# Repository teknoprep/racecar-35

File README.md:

# racecar-35

Two-MCU dash for a track car.

**Latest Rev C target:** add a third MCU—an on-board ESP32-S3 WiFi coprocessor—to
upload directly from Teensy SD over local SPI, while the screen keeps WiFi for
unchanged OTA and optional upload fallback. Add a replaceable CR2032 on Teensy VBAT
for RTC retention. This is an architecture update, **not an implemented new uplink**;
see [WiFi/RTC requirements](hardware/teensy-integrated-revc/WIFI_RTC_ARCHITECTURE.md).
Rev C has an **internal WiFi PCB antenna** and **all screw terminals on the LEFT
edge**, labelled by function/pin. **Actual 130 × 140 mm routed electrical CAD,
Gerber/drill ZIP, BOM, assembly documents and an assembled view now exist:**
[Rev C engineering prototype](hardware/teensy-integrated-revc/README.md).
It passes ERC/DRC/netlist checks but is unbuilt and not independently approved;
new WiFi firmware, oil/coolant conversions and bench validation remain.
A/B are retired under `hardware/_archive/`, not alternative orderable designs.

**WiFi-only on the CrowPanel since v0.1.148.** Ethernet/W5500 support
and the Internet-route setting have been removed. WiFi credentials/status are
always visible; old saved Ethernet selections are ignored. NTP/OTA/uploads run
through the screen. See [CLAUDE.md](CLAUDE.md) and [BUILD.md](BUILD.md) for current
architecture/toolchains; much of the original overview below is historical.
The integrated Rev C board is an unbuilt electrical prototype. **v0.1.149 source adds
opt-in AFR/lambda logging from the external AEM 30-0300 gauge output** (WHITE signal
and BROWN reference), not a direct oxygen sensor. A protected/scaled ADC input
is implemented in Rev C with clamps and powered-off isolation, but requires
independent review and physical validation. See
[AFR_INTERFACE.md](hardware/teensy-integrated-revc/AFR_INTERFACE.md).

```
+--------------+   Serial2 (UART)   +--------------+   Serial3 (UART)   +--------------+
|              |  pin 7 RX2 / 8 TX2 |              | pin 14 TX3 / 15 RX |              |
|  u-blox GNSS | <----------------> | Teensy 4.1   | -----------------> | CrowPanel S3 |
|              |   38400/9600 baud  |              |    115200 baud     |  7" 800x480  |
+--------------+                    +--------------+                    +--------------+
                                                                         (LovyanGFX UI)
```

The Teensy reads GNSS PVT data from a SparkFun u-blox module and publishes
ASCII CSV lines on Serial3. The CrowPanel ESP32-S3 listens on UART0 and
renders the dash with LovyanGFX. UART is one-way, Teensy → CrowPanel.

## Repository layout

| Path | Project | Target |
| --- | --- | --- |
| `platformio.ini`, `src/main.cpp` | Teensy firmware | Teensy 4.1 |
| `crowpanel-ui/platformio.ini`, `crowpanel-ui/src/main.cpp` | Dash UI | CrowPanel ESP32-S3 7" v3.0 |

Each subproject is its own PlatformIO env. Build them from their own
directory.

## Wire protocol

ASCII CSV lines, `\n`-terminated, 115200 8N1, ~5 Hz:

```
GPS,<fix>,<sats>,<lat_deg>,<lon_deg>,<speed_mph>,<heading_deg>
```

| Field | Meaning |
| --- | --- |
| `fix` | 0=None 1=DR 2=2D 3=3D 4=3D+DR 5=Time-only |
| `sats` | satellites in view |
| `lat_deg`, `lon_deg` | decimal degrees, 6 decimals |
| `speed_mph` | mph, 1 decimal |
| `heading_deg` | course over ground in degrees, 1 decimal |

Example: `GPS,3,12,40.123456,-74.123456,67.5,123.4`

## Wiring

| Link | From | To |
| --- | --- | --- |
| GPS → Teensy | u-blox TX | Teensy pin 7 (Serial2 RX) |
| Teensy → GPS | Teensy pin 8 (Serial2 TX) | u-blox RX |
| Teensy → Dash | Teensy pin 14 (Serial3 TX) | CrowPanel UART0 RX (GPIO 44) |
| Dash → Teensy | Teensy pin 15 (Serial3 RX) | CrowPanel UART0 TX (GPIO 43) |
| Common ground | Teensy GND | CrowPanel GND |
| Power | USB-C to CrowPanel | (Teensy powered separately by its own USB) |

Teensy ↔ CrowPanel is two devices both on 3.3 V logic — no level shifter.
A common ground is required.

## Flashing

### Teensy firmware

```powershell
pio run -t upload
```

The first time, you may need to physically tap the program button on the
Teensy. After that, `teensy_reboot` resets the board over USB.

### CrowPanel firmware

> [!IMPORTANT]
> **Disconnect the two UART jumpers between the Teensy and the CrowPanel
> before flashing the CrowPanel.** UART0 (GPIO 43/44) is shared with the
> CH340 USB-serial chip used to upload firmware. If the Teensy is
> connected, both devices will drive the same wire and the upload will
> fail or corrupt.

```powershell
cd crowpanel-ui
pio run -t upload
```

After the upload finishes ("Hash of data verified"), unplug USB-C, wire
the Teensy back in, then power the CrowPanel via USB-C again.

## End-to-end smoke test

1. Flash both firmwares (Teensy first or CrowPanel first, doesn't matter).
2. Wire everything per the table above. Double-check common GND.
3. Power the CrowPanel via USB-C. The dash should boot and show 0.0 mph
   with `LINK STALE` in red — that's correct: nothing on the wire yet.
4. Plug in the Teensy. Within a second, `LINK` should turn green and you
   should see the speed/heading/lat/lon updating at ~5 Hz, even with no
   GPS fix yet (those fields will read 0 until `FIX` shows `2D`/`3D`).
5. Take it outside or near a window. `FIX` will go yellow → green and
   `SATS` will climb as the module gets a fix.

## Debugging

- Open `pio device monitor` on the Teensy to see the same CSV stream the
  Teensy is sending — useful for confirming the GPS half is working
  before chasing UART issues on the dash side.
- Open `pio device monitor` on the CrowPanel (with the Teensy
  disconnected, and a `Serial.print` of incoming bytes added if you want
  to see what's hitting UART0). Note that with `ARDUINO_USB_CDC_ON_BOOT=0`
  the CrowPanel's `Serial` object IS UART0 — the same wire the Teensy
  uses — so you can't tap it from USB and the Teensy at the same time.
- If the panel boots black, retry the power-only test (USB-C only, no
  Teensy wires) to confirm the panel itself is alive before suspecting
  firmware.

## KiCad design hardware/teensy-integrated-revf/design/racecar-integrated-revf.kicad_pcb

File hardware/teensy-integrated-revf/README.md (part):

# Rev F — four-layer integrated trunk logger

**UNBUILT ENGINEERING PROTOTYPE. NOT INDEPENDENTLY REVIEWED OR PHYSICALLY
VALIDATED.** A clean CAD report is not electrical approval, a thermal test, an
RF measurement, or evidence that the board works.

Produced to close three gaps in Rev C: the missing Raspberry Pi video UART and the
missing throttle-position and brake-pressure analog inputs.

**Rev E closed two more:** the 5 V rail is **our own TPS54560B converter** instead of a
Pololu module that could not be sourced, and the **car's own input voltage is measured on
the board** instead of being inferred from the ECU or a Bluetooth dongle.

**Rev F closes the CAN gap.** The external SN65HVD230 plug-in module and its `J7` header
are **deleted**; a **TCAN1042HGV-Q1** is soldered on with its **STB pin hard-tied to GND**,
and `J14` presents `CANH` / `CANL` / `GND` with switchable split termination. See
[Onboard CAN (Rev F)](#onboard-can-rev-f--no-plug-in-module).

## Deliverable

- **`Racecar-RevF-GERBERS-ENGINEERING-PROTOTYPE.zip`** — 11 Gerber layers
  (4 copper + both masks/silkscreens/pastes + Edge.Cuts), separate metric
  **PTH and NPTH** Excellon drills with maps, schematic PDF, BOM, assembly
  positions CSV, fabrication/assembly/bring-up notes, editable CAD, validation
  reports and a SHA-256 manifest. Verified CRC and per-file hashes.
- **`Racecar-RevF-3D.html`** — the whole board in 3D as **one self-contained file**
  (1.5 MB): orbit/zoom, a clickable list of what is fitted, and labels on the parts.
  No server, no CDN, no network — open it from anywhere, or send it to someone.
- **`Racecar-RevF-3D.glb`** — the same board as a standard glTF model (5.4 MB),
  for Blender, Windows 3D Viewer, any online glTF viewer, a fab/shop or a case
  designer. Plain glTF 2.0, no extensions to install.
- **`Racecar-RevF-3D-preview.png`** — still image of the viewer, for documents.

### Rebuilding the 3D outputs

```bash
cd hardware/teensy-integrated-revf
python3 electrical/export3d.py      # presentation copy + Racecar-RevF-3D.glb (+ raw copper)
python3 electrical/make_3d_share.py # the single-file viewer (needs node + a local three)
cp render/Racecar-RevF-3D.glb render/Racecar-RevF-3D.html .
/home/chris/racecar-tools/servervenv/bin/python3 electrical/render_stills.py
                                    # render/check/{top,angle}.png + Racecar-RevF-3D-preview.png
```

The 3D outputs carry whatever silkscreen `design/` holds, so re-run all four steps after a
silk change (the stills used to lag the board: they still showed the 2026-10-11 silk).

Both scripts work on a **copy**; the routed CAD in `design/` is hashed before and
after and is never modified by them. Every model substitution, the generated bodies and
the caveats are recorded in `render/3D-EXPORT-REPORT.json` for audit.

**How the bodies were obtained (and what is not real):**

* KiCad's official 3D library supplies the STEP bodies (`sudo apt-get install
  kicad-packages3d`). Without it, `kicad-cli` cannot export component bodies at all —
  **VRML models are ignored** by the GLB/STEP exporters.
* **No vendor model exists** for a Teensy 4.1, a u-blox NEO-M9N or a Littelfuse Nano2
  holder, so those are **generated boxes** of the correct size and colour (the Teensy is
  built from nine of them: two 1×24 sockets, the board, MCU, flash, micro-USB, microSD and
  the two pin fields).
* Two library parts are replaced by a **named near-twin** because the exact model is not
  in the package: the SMA jack → `SMA_Molex_73251-2200_Horizontal`, the SOIC-8-EP buck →
  `HSOP-8-1EP_3.9x4.9mm_P1.27mm_EP2.41x3.1mm`. The 901-143 is a right-angle THROUGH-HOLE
  jack (a straight jack turned on its side: square body standing on 5 pins, barrel out
  sideways past the board edge); the Molex twin has the same construction, the same pin
  pattern (centre + 4 grounds at ±2.54 mm) and the same frame, so it needs no transform.
  Its barrel is ~5 mm longer — take enclosure dimensions from Amphenol's drawing. (Until
  2026-10-20 the twin was the 132289 **edge-mount**, a flat bracket that clamps over a board
  edge, and it was also rotated 90° — it rendered lying along the top edge. Render-only:
  the copper/Gerbers come from the footprint, KiCad's stock 901-143 placed exactly on its
  own board-edge marker, y = −4.5 mm.) `SUBST_TRANSFORM` in `export3d.py` exists for a
  twin whose frame does NOT match; check any new twin against its own stock footprint.
* Consequently the 3D model is **illustrative**: it is not a mechanical, fit, RF or thermal
  model, it is not evidence that the board works, and it does not change the fact that
  Rev F is an unbuilt, unmeasured, not-independently-reviewed prototype.

## Status at export

| Check | Result |
|---|---|
| ERC | **0 violations** |
| DRC (full severity) | **0 violations** |
| Unconnected items | **0** |
| Pin-contract / geometry / calculation assertions | **749 passed** |
| Schematic ↔ PCB connected pads | **538 agree** |
| Footprints / nets / routed items | 193 / 104 / 1,647 segments with 131 vias |

## Onboard CAN (Rev F) — no plug-in module

**Problem (root-caused on the bench, 2026-10-04).** The external CAN module on `J7` received
frames but **never drove the bus**, so it never ACKed and the sender retransmitted ~3,800
identical frames/s. The module — sold as an "SN65HVD230" — actually carries a
**TJA1051T/3-class chip**, and the two share a footprint but not a pinout: pin 3 (VCC) needs
**5 V** (the driver locks out below 4.5 V), pin 5 is **VIO** not Vref, and pin 8 is **S /
standby**. Driven the SN65HVD230 way (VCC = 3.3 V, pin 5 floating, pin 8 floating) the driver
was locked out, and a floating VIO was phantom-fed from TXD (~2.1 V), so RXD collapsed
whenever TXD went low — an internal echo that made every Teensy-side self-test *look* like a
working transmitter. Rewired as VCC 5 V / pin 5 3.3 V / pin 8 GND it ran at exactly 200
frames/s, both ids, 0 errors. Full analysis:
`../../CAN-TRANSCEIVER-FINDINGS-2026-10-04.md`.

A plug-in module therefore has three failure modes the carrier cannot control: the wrong chip
on the board, the wrong wiring to it, and no 5 V rail on a USB-only bench. Rev F removes all
three by **soldering down a known part with the rails and mode pin hard-wired**.

**Fix: a soldered transceiver whose supply and mode pin cannot be wrong.**

* `U21` = **TI TCAN1042HGVDRQ1** (`TCAN1042HGV-Q1`), SOIC-8, AEC-Q100, ±70 V bus fault
  protection, **`VIO` on pin 5** for 3.3 V logic. **Authorized distribution only; no
  substitution without written approval.** Approved alternates, in order: `TCAN1042VDRQ1`,
  then NXP `TJA1051T/3/1J` (its pin 8 `S` must also go to GND).
  ⚠️ **The `V` suffix is mandatory** — it *is* the VIO pin. `TCAN1042DRQ1` / `TCAN1042HDRQ1`
  / `TCAN1042GDRQ1` have **pin 5 = NC**, so RXD would swing to 5 V and destroy Teensy pin 23.
  **Never** an SN65HVD23x, a plain `TJA1051T` (no `/3`), a `TJA1050`, or any clone.
* Pins: 1 `TXD`→`CAN_TX` (Teensy pin 22 = U1 pad 29), 2 `GND`, 3 `VCC`→`+5V_MAIN`,
  4 `RXD`→`CAN_RX` (Teensy pin 23 = U1 pad 28), 5 `VIO`→`+3V3_MCU`, 6 `CANL`, 7 `CANH`,
  **8 `STB` hard-tied to GND**. `STB` high is standby = receive-only with no ACK — exactly
  the state being designed out — so there is no pull-up, no resistor and no jumper on it.
* Decoupling `C49`/`C50` 100 nF at VCC/VIO and `C51` 1 µF on VCC. `U21` needs the 5 V rail,
  so **CAN does not work on Teensy-USB power alone**; the bench needs `J1` powered. That a
  powered `VIO` with `VCC` off (USB-only bench) leaves the bus passive must be confirmed
  against the TCAN1042 datasheet — this document does not claim it.
* `J14` "CAN" (Phoenix **1729021**, 3-position 5.08 mm, the same family as J4/J11/J12):
  **1 `CANH`, 2 `CANL`, 3 `GND`** (signal-ground reference to the ECU).
* **Switchable split termination**: `R58` + `R59` = two **60.4 Ω 1 %** in series (120.8 Ω
  across the pair), midpoint to GND through `C52` 4.7 nF (50 V), in series with **`JP2`**.
  **Fit the JP2 shunt only if this board is an end of the bus.**
* `D25` = **onsemi NUP2105LT1G** dual CAN TVS at `J14` (alternates: Nexperia `PESD2CAN,215`
  or TI `ESD2CAN24DBZRQ1`).
* Test points `TP6` (`CAN_TX`) and `TP7` (`CAN_RX`). `J7` and its BOM line are deleted —
  two RXD drivers would otherwise fight on U1 pad 28.
* **No common-mode choke.** The optional TDK `ACT45B-510-2P-TL003` with 0 Ω bypass links is
  **omitted**: there was no room for it and its links beside `U21` without displacing the
  analog front ends. Add it on a future revision only if conducted/radiated emissions
  measurements show it is needed.
* **No firmware change:** 500 kbit/s, normal (ACKing) mode. The TCAN1042's TXD dominant
  time-out (≈1 ms) will cut the firmware's `CANHOLD` diagnostic short — that is expected,
  real CAN traffic never holds dominant that long.
* **Not claimed:** automotive transient qualification or a working vehicle bus. The ESD
  and termination parts are selected but `CAN` has not been built, measured or reviewed.

**Also new in Rev F — the silkscreen was restored.** Rev C–E's generator moved *every*
footprint's silk to `F.Fab`, which left the fabricated board with **no component markings
at all** (0 of 193 footprints had any `F.SilkS`): no pin-1 dots, no diode cathode bands, no
electrolytic polarity marks, no outlines. Rev F keeps them (only the ESP32 module's
outline, which crosses the antenna-notch edge, stays on `F.Fab`) — so `U21` now carries a
pin-1 dot and every diode/electrolytic shows its polarity on the board.
* **Layout limitation of this pass:** the autorouter routed the logic pair
  `CAN_TX`/`CAN_RX` at roughly **80–90 mm** over two inner layers and `CANH`/`CANL` at
  roughly **30–45 mm** (`U21`↔`J14` ≈23 mm). Longer than a hand layout would give and
  harmless at 500 kbit/s — the lengths vary between autorouter runs and are quoted as a
  range — but a future pass should shorten the logic-side pair to U1 pads 29/28.

## Rev E — our own 5 V rail and the on-board input monitor

* **The 5 V rail is our own converter.** U2 is a **TI TPS54560B** 60 V / 5 A asynchronous
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
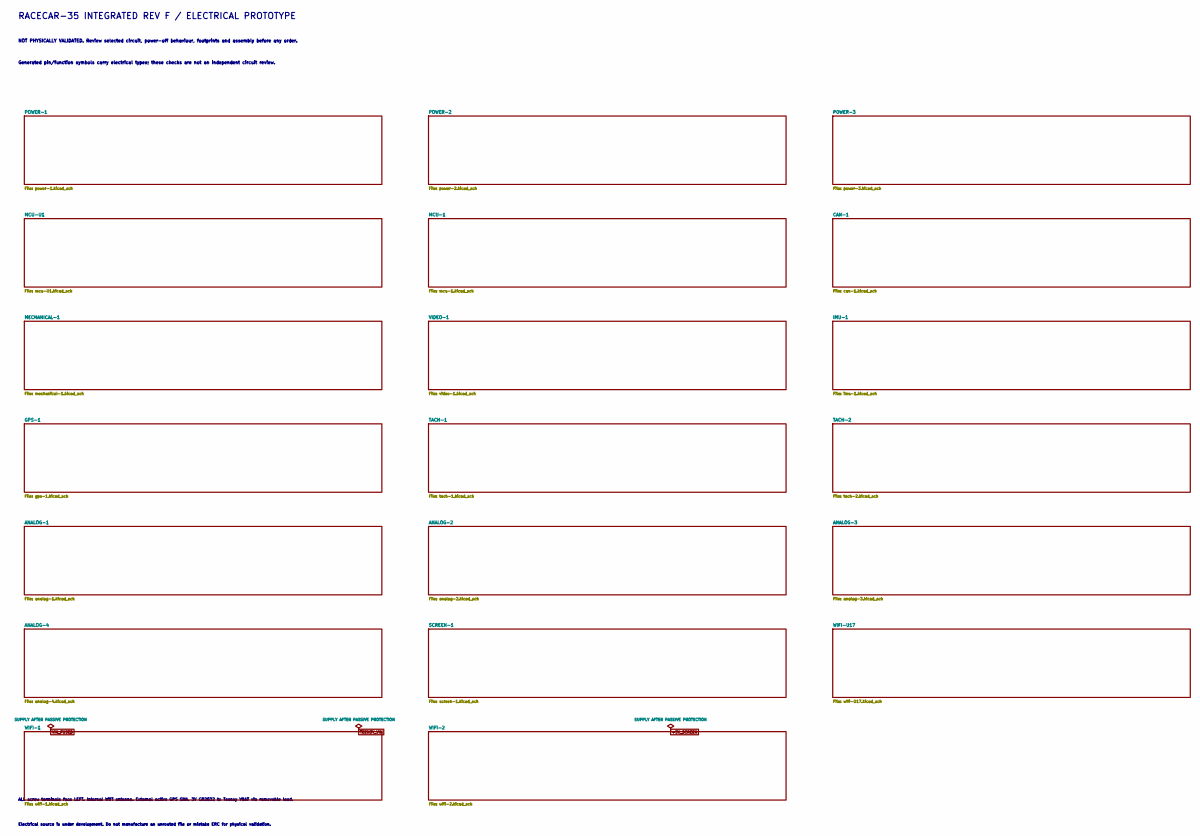
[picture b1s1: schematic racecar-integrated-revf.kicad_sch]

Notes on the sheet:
RACECAR-35 INTEGRATED REV F / ELECTRICAL PROTOTYPE
NOT PHYSICALLY VALIDATED. Review selected circuit, power-off behaviour, footprints and assembly before any order.
Generated pin/function symbols carry electrical types; these checks are not an independent circuit review.
ALL screw terminals face LEFT. Internal WiFi antenna. External active GPS SMA. 3V CR2032 to Teensy VBAT via removable lead.
Electrical source is under development. Do not manufacture an unrouted file or mistake ERC for physical validation.

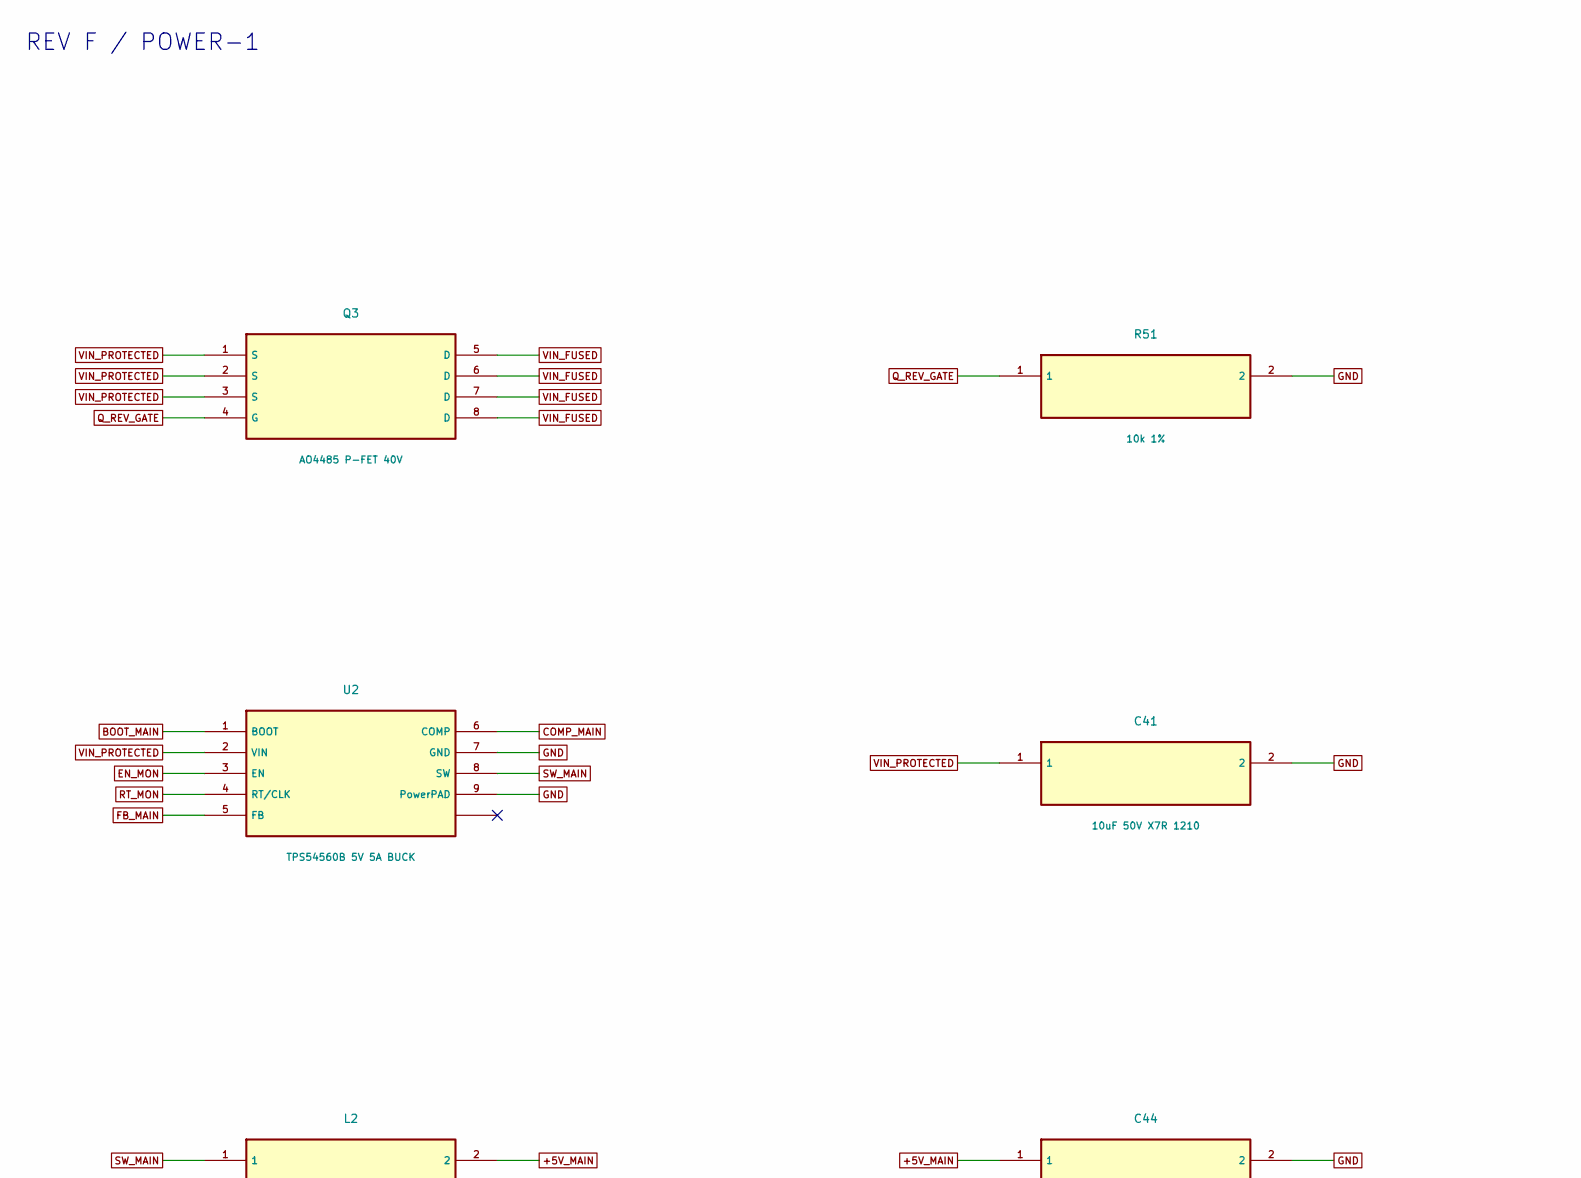
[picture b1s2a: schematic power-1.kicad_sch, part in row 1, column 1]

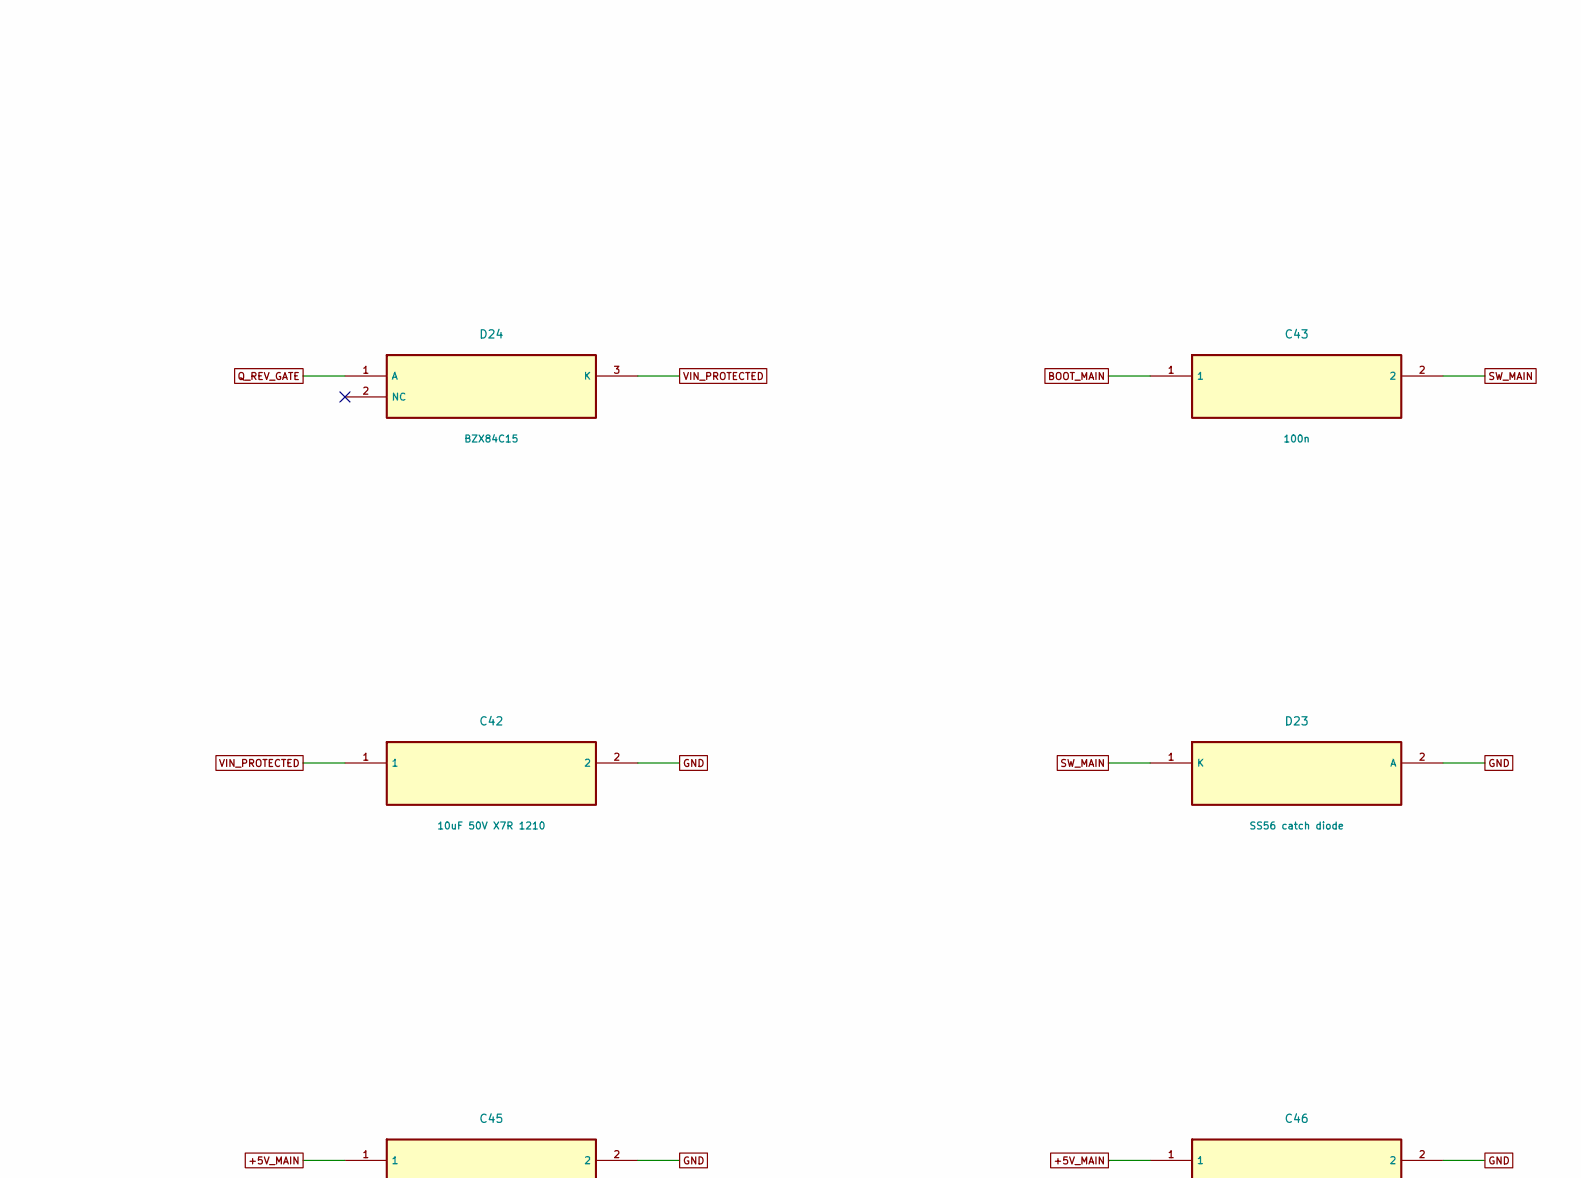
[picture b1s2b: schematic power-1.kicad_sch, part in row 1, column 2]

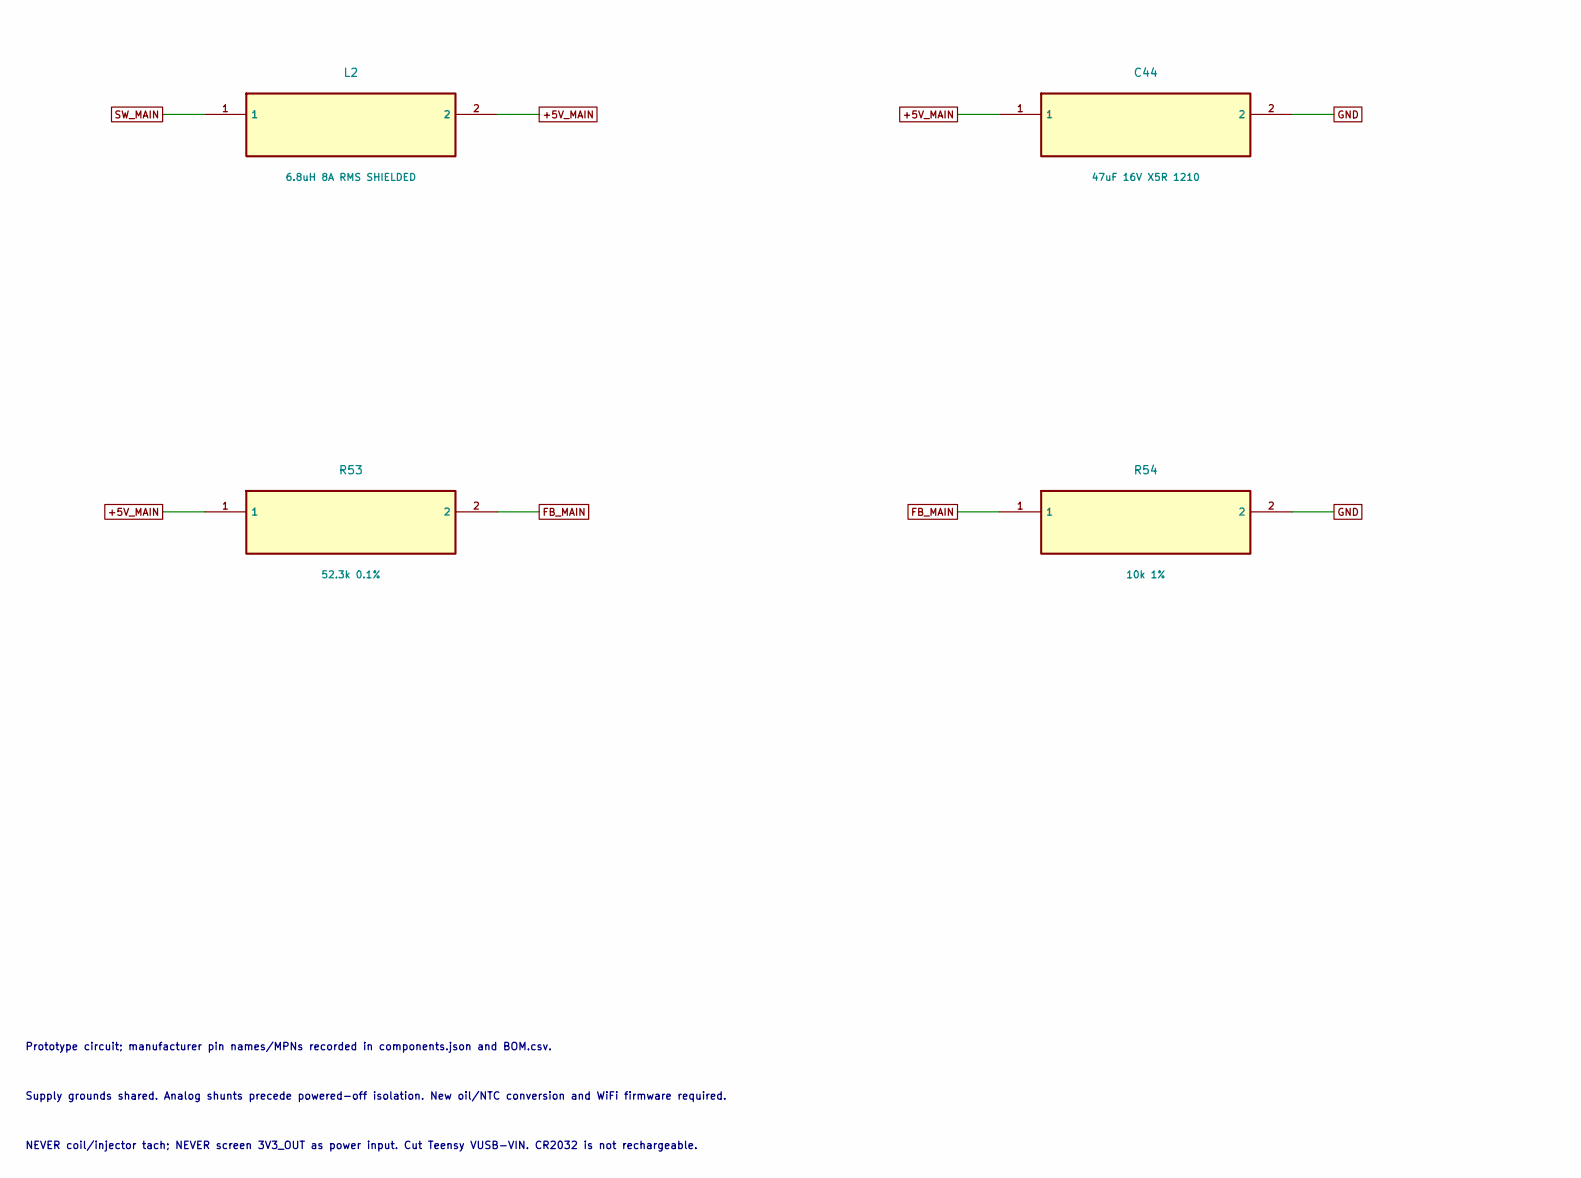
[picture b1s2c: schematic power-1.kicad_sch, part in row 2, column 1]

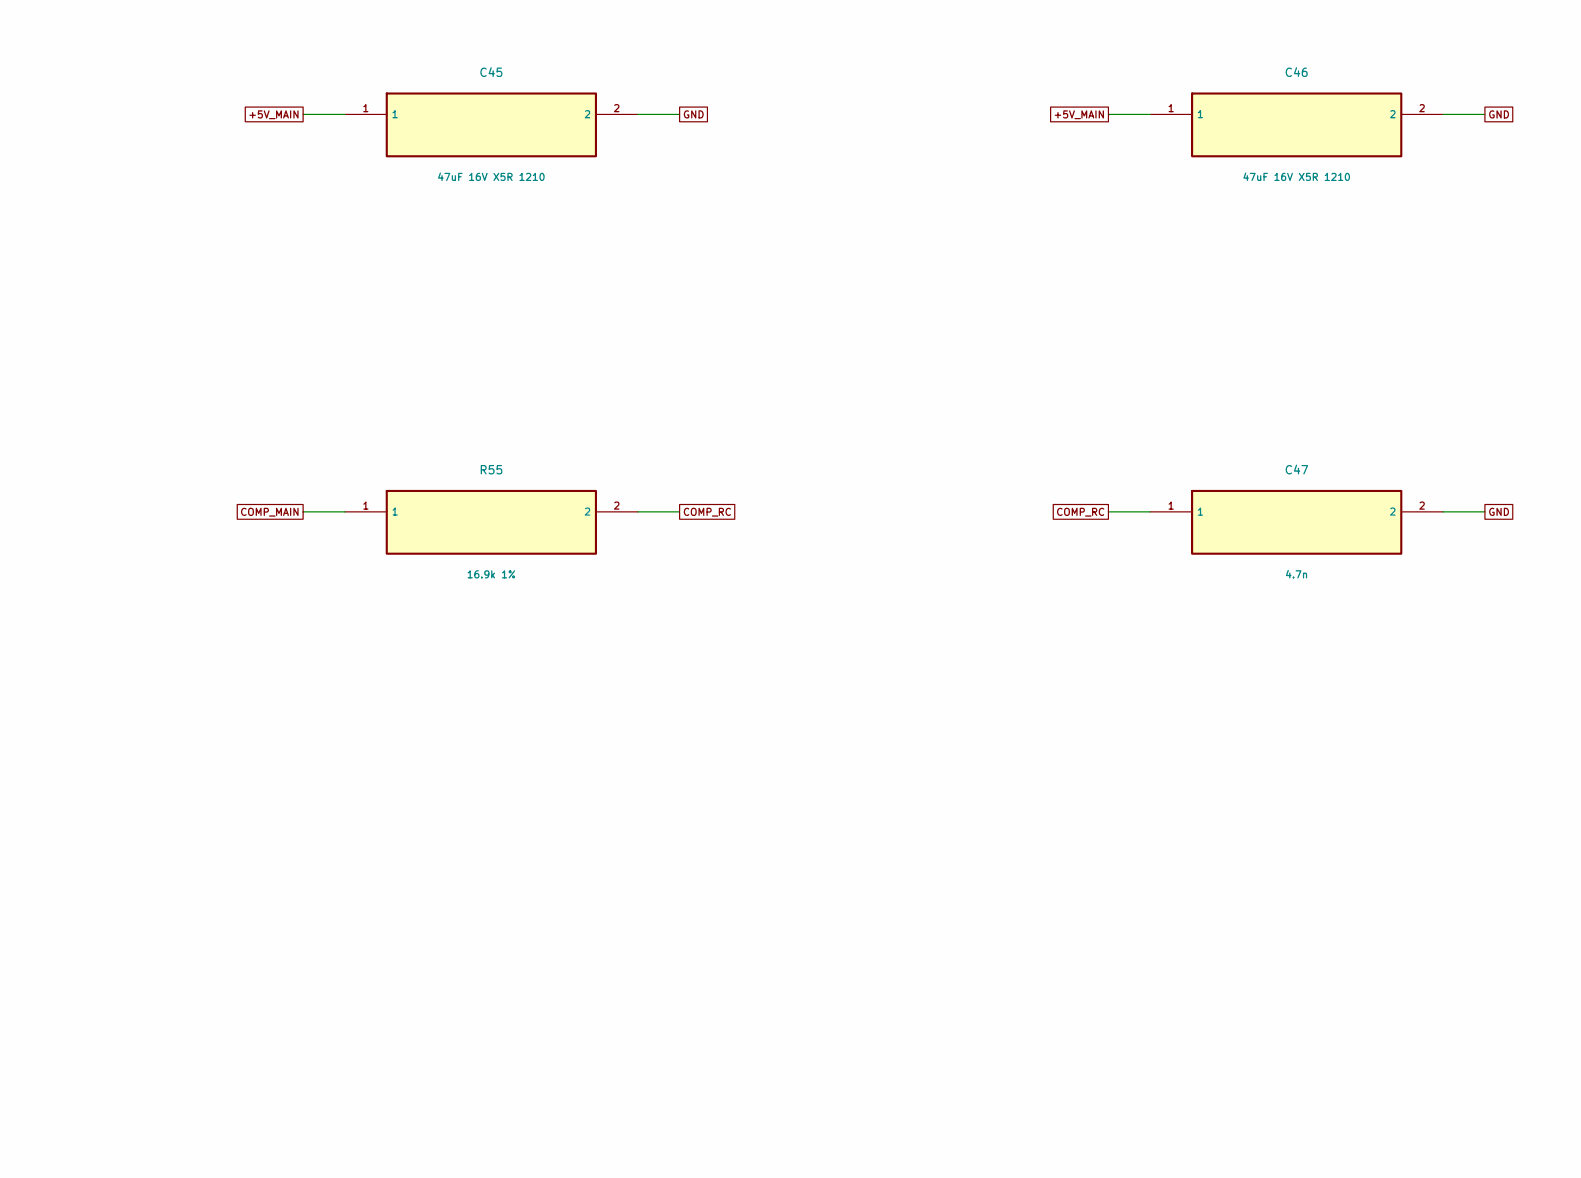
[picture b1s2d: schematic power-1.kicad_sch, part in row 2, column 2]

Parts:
C41, C42: 10uF 50V X7R 1210; C_1210_3225Metric
C43: 100n; C_0805_2012Metric
C44, C45, C46: 47uF 16V X5R 1210; C_1210_3225Metric
C47: 4.7n; C_0805_2012Metric
D23: SS56 catch diode; D_SMB
D24: BZX84C15; SOT-23
L2: 6.8uH 8A RMS SHIELDED; L_Vishay_IHLP-4040
Q3: AO4485 P-FET 40V; SOIC-8_3.9x4.9mm_P1.27mm
R51, R54: 10k 1%; R_0805_2012Metric
R53: 52.3k 0.1%; R_0805_2012Metric
R55: 16.9k 1%; R_0805_2012Metric
U2: TPS54560B 5V 5A BUCK; SOIC-8-1EP_3.9x4.9mm_P1.27mm_EP2.41x3.3mm

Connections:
+5V_MAIN: C44.1, C45.1, C46.1, L2.2, R53.1; also elsewhere on the board
BOOT_MAIN: C43.1, U2.1 (BOOT)
COMP_MAIN: R55.1, U2.6 (COMP); also elsewhere on the board
COMP_RC: C47.1, R55.2
EN_MON: U2.3 (EN); also elsewhere on the board
FB_MAIN: R53.2, R54.1, U2.5 (FB)
GND: C41.2, C42.2, C44.2, C45.2, C46.2, C47.2, D23.2 (A), R51.2, R54.2, U2.7 (GND), U2.9 (PowerPAD); also elsewhere on the board
Q_REV_GATE: D24.1 (A), Q3.4 (G), R51.1
RT_MON: U2.4 (RT/CLK); also elsewhere on the board
SW_MAIN: C43.2, D23.1 (K), L2.1, U2.8 (SW)
VIN_FUSED: Q3.5 (D), Q3.6 (D), Q3.7 (D), Q3.8 (D); also elsewhere on the board
VIN_PROTECTED: C41.1, C42.1, D24.3 (K), Q3.1 (S), Q3.2 (S), Q3.3 (S), U2.2 (VIN); also elsewhere on the board

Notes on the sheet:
REV F / POWER-1
Prototype circuit; manufacturer pin names/MPNs recorded in components.json and BOM.csv.
Supply grounds shared. Analog shunts precede powered-off isolation. New oil/NTC conversion and WiFi firmware required.
NEVER coil/injector tach; NEVER screen 3V3_OUT as power input. Cut Teensy VUSB-VIN. CR2032 is not rechargeable.

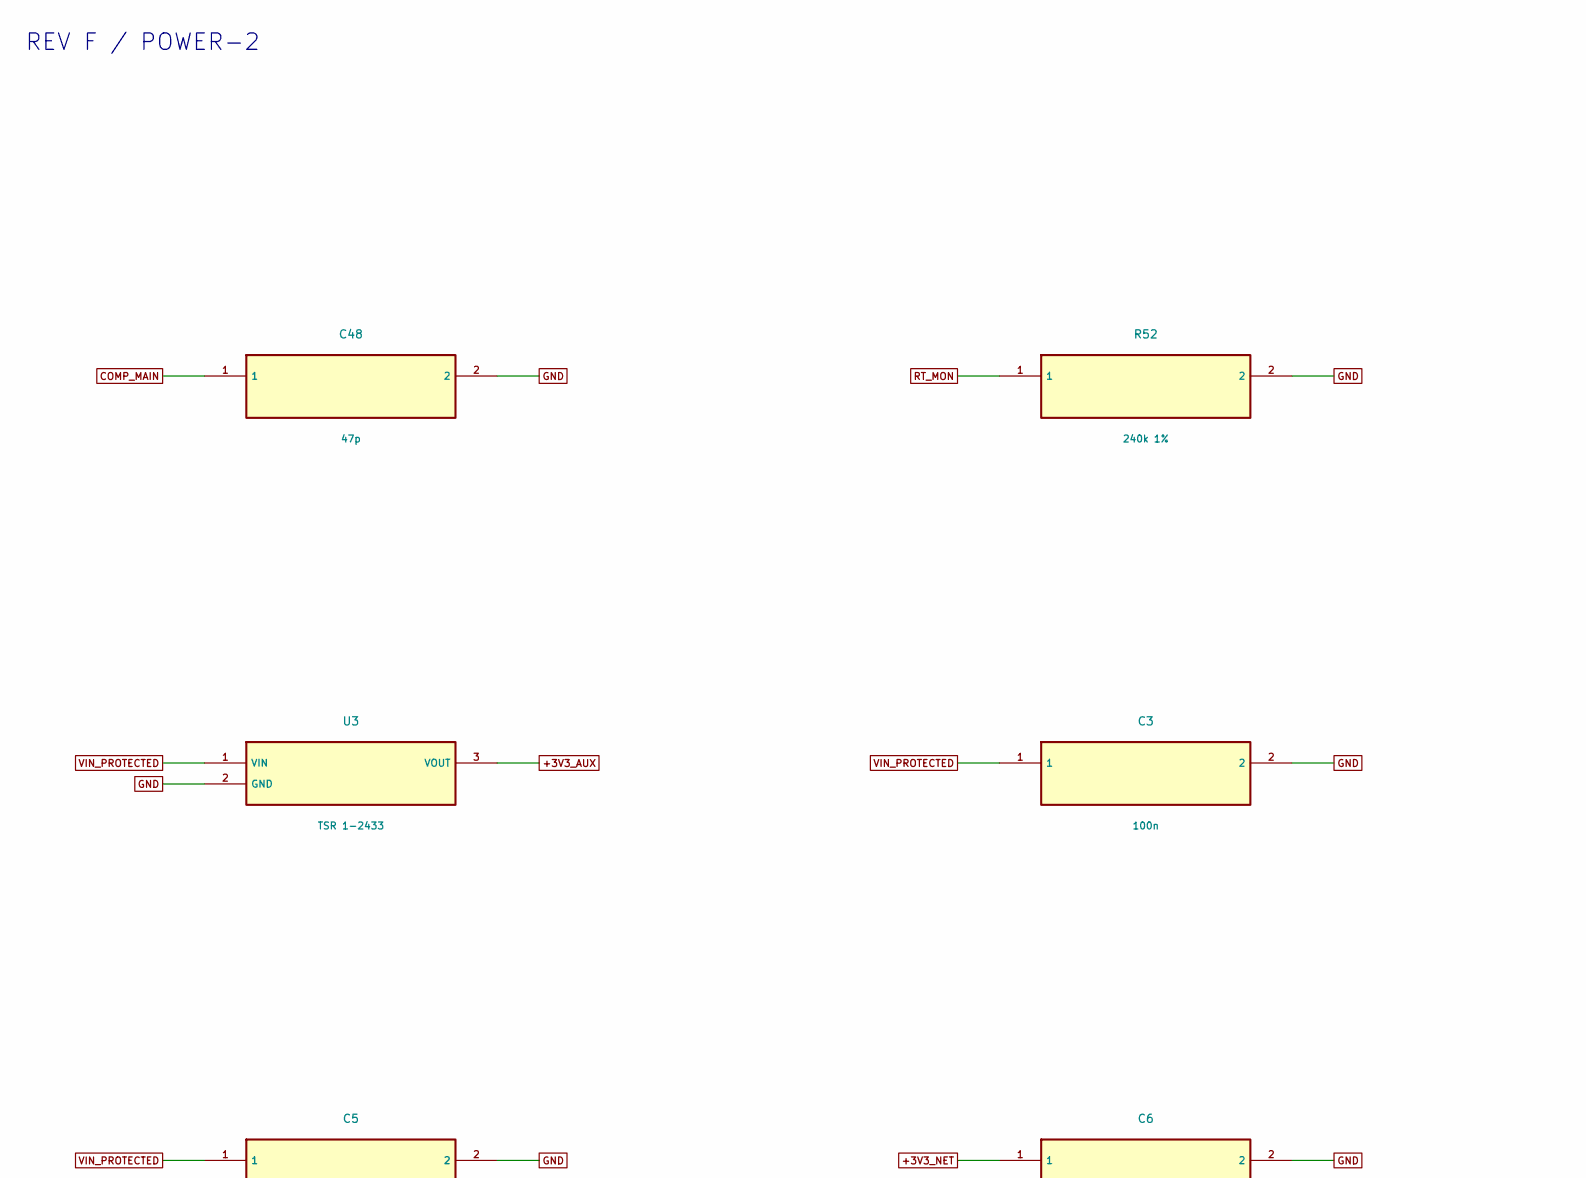
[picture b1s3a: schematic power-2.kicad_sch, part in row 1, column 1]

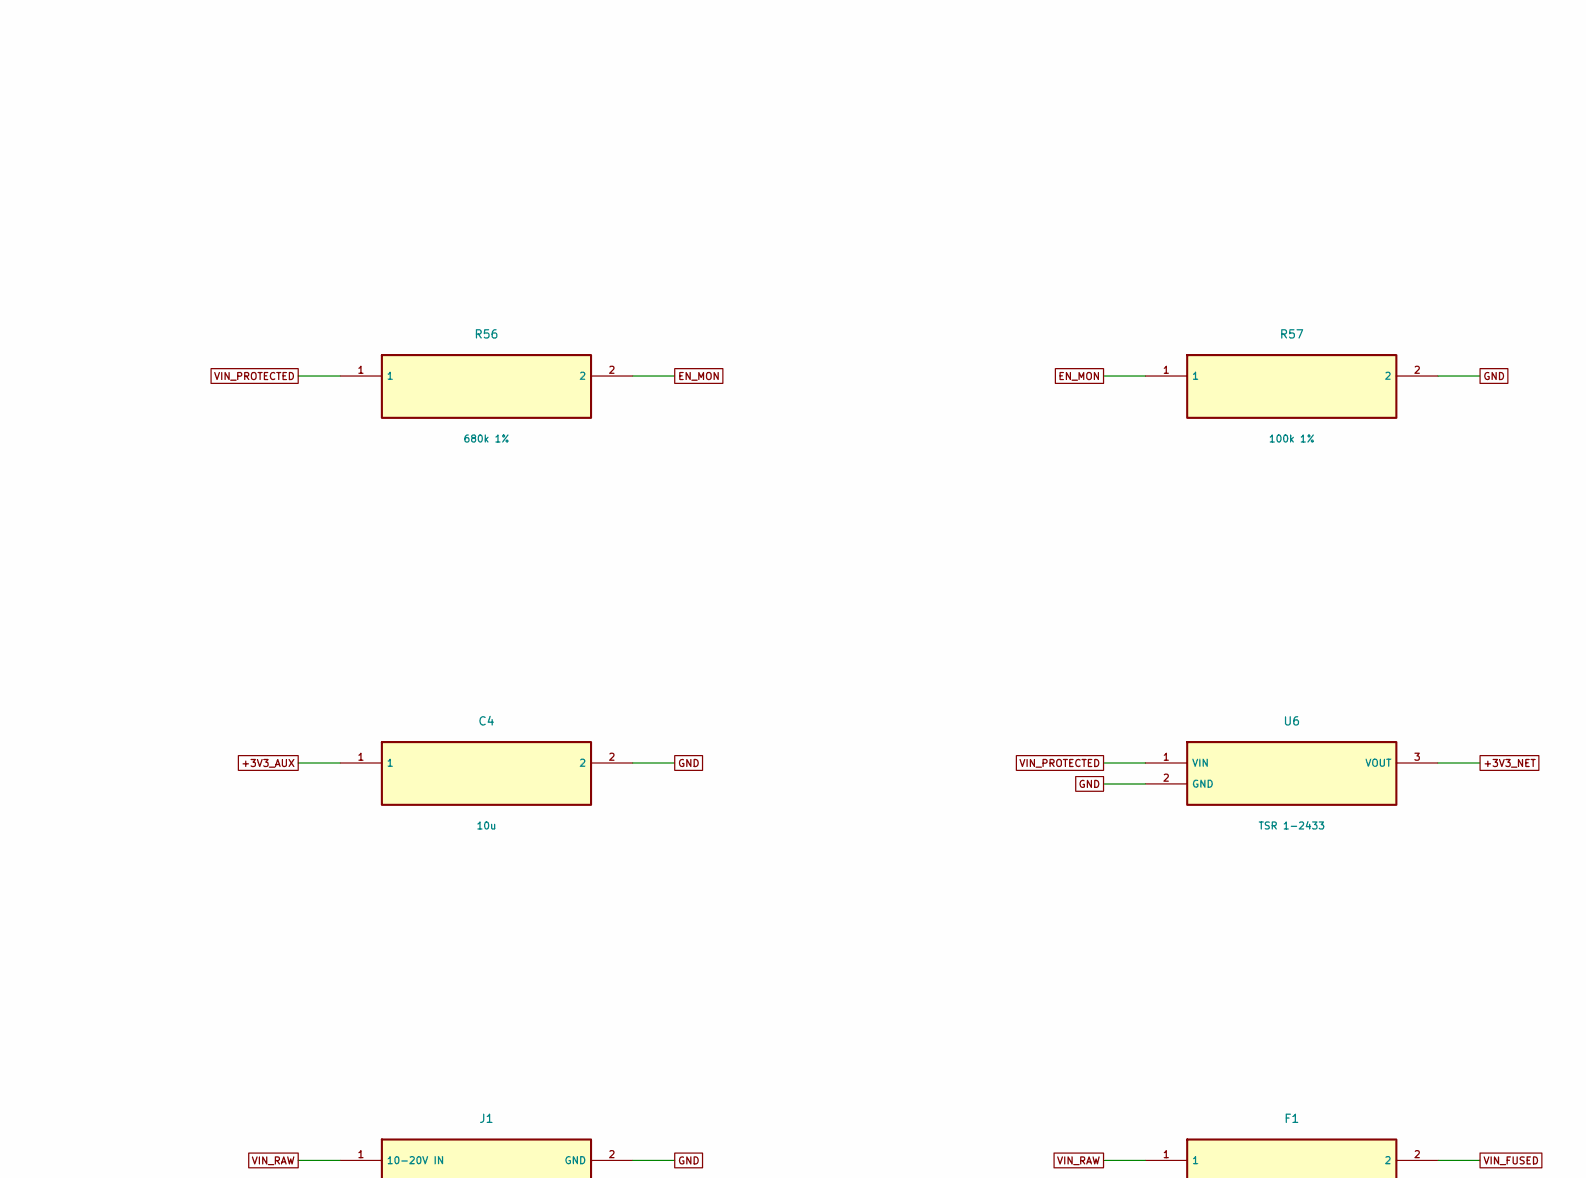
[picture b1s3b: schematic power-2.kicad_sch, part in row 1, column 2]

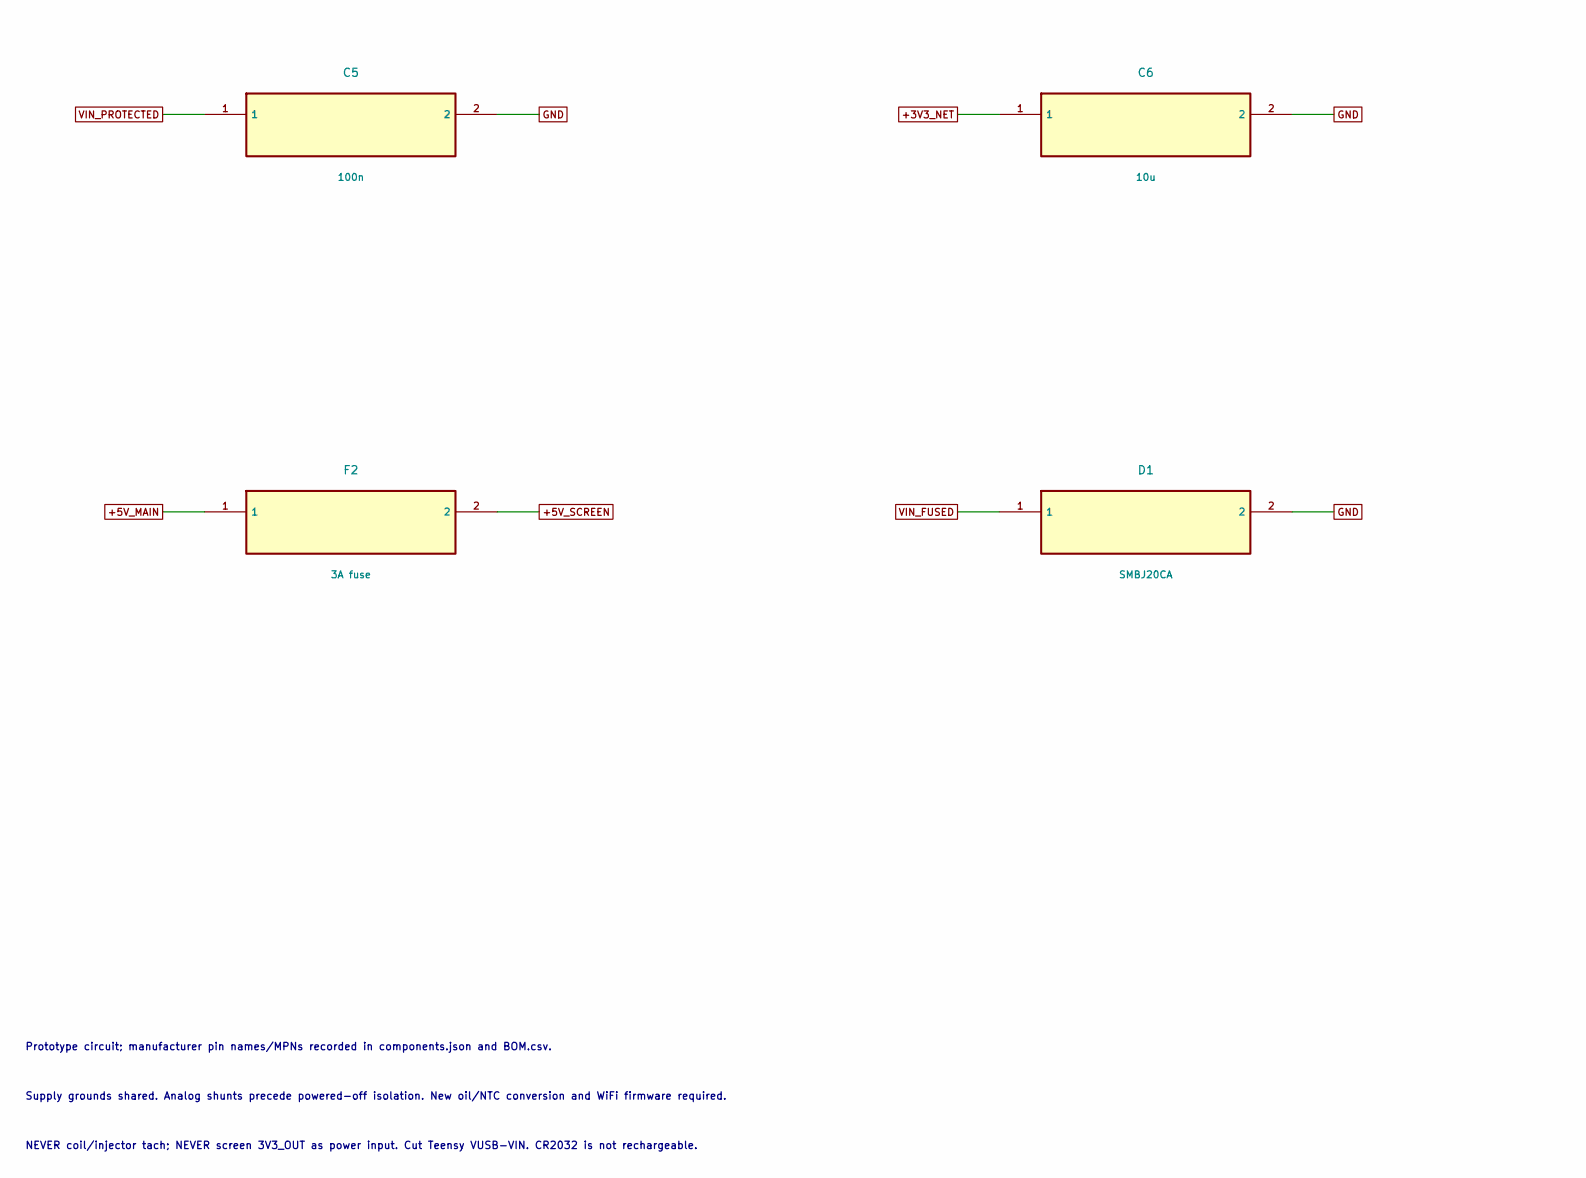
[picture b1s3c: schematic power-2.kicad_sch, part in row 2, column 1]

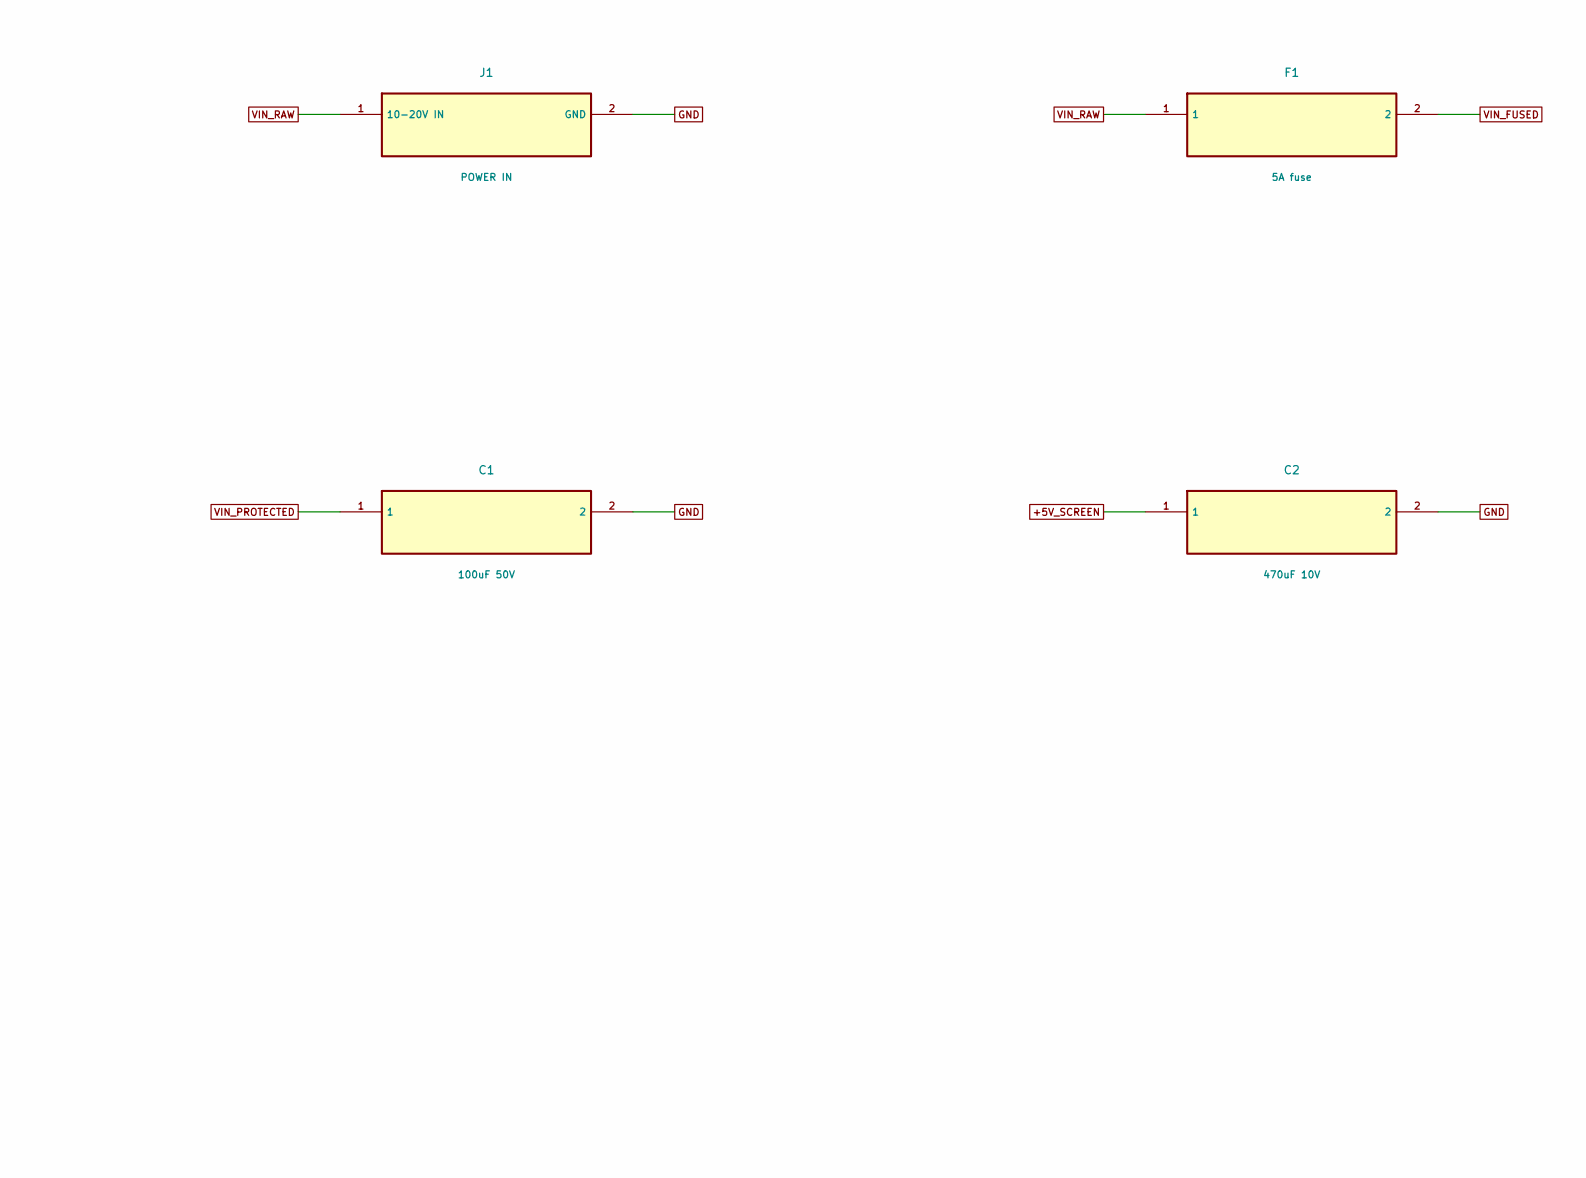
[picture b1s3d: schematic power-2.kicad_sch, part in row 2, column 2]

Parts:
C1: 100uF 50V; CP_Radial_D8.0mm_P3.50mm
C2: 470uF 10V; CP_Radial_D8.0mm_P3.50mm
C3, C5: 100n; C_0805_2012Metric
C4, C6: 10u; C_0805_2012Metric
C48: 47p; C_0805_2012Metric
D1: SMBJ20CA; D_SMB
F1: 5A fuse; Fuse_Littelfuse-NANO2-451_453
F2: 3A fuse; Fuse_Littelfuse-NANO2-451_453
J1: POWER IN; TerminalBlock_Phoenix_MKDS-1,5-2-5.08_1x02_P5.08mm_Horizont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
R52: 240k 1%; R_0805_2012Metric
R56: 680k 1%; R_0805_2012Metric
R57: 100k 1%; R_0805_2012Metric
U3, U6: TSR 1-2433; Converter_DCDC_TRACO_TSR-1_THT

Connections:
+3V3_AUX: C4.1, U3.3 (VOUT); also elsewhere on the board
+3V3_NET: C6.1, U6.3 (VOUT); also elsewhere on the board
+5V_MAIN: F2.1; also elsewhere on the board
+5V_SCREEN: C2.1, F2.2; also elsewhere on the board
COMP_MAIN: C48.1; also elsewhere on the board
EN_MON: R56.2, R57.1; also elsewhere on the board
GND: C1.2, C2.2, C3.2, C4.2, C5.2, C6.2, C48.2, D1.2, J1.2 (GND), R52.2, R57.2, U3.2 (GND), U6.2 (GND); also elsewhere on the board
RT_MON: R52.1; also elsewhere on the board
VIN_FUSED: D1.1, F1.2; also elsewhere on the board
VIN_PROTECTED: C1.1, C3.1, C5.1, R56.1, U3.1 (VIN), U6.1 (VIN); also elsewhere on the board
VIN_RAW: F1.1, J1.1 (10-20V IN)

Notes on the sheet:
REV F / POWER-2
Prototype circuit; manufacturer pin names/MPNs recorded in components.json and BOM.csv.
Supply grounds shared. Analog shunts precede powered-off isolation. New oil/NTC conversion and WiFi firmware required.
NEVER coil/injector tach; NEVER screen 3V3_OUT as power input. Cut Teensy VUSB-VIN. CR2032 is not rechargeable.
